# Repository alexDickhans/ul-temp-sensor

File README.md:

# Adaptive BLE Sensor Node System

A complete IoT sensor system featuring adaptive power management, BLE communication, and data logging. The system consists of a Raytac MDBT50Q (nRF52840) sensor node and a Raspberry Pi host application.

## 🏗️ System Architecture

```
┌─────────────────┐    BLE Advertisement    ┌─────────────────┐
│   Sensor Node   │ ──────────────────────► │  Raspberry Pi   │
│                 │                         │     Host        │
│ • nRF52840      │                         │                 │
│ • BME280        │                         │ • BLE Scanner   │
│ • Battery       │                         │ • Data Logger   │
│ • Adaptive PM   │                         │ • SQLite DB     │
└─────────────────┘                         └─────────────────┘
```

## 📋 Features

### MCU Firmware (nRF52840)
- **Adaptive Power Management**: 4-tier power system based on battery voltage
- **BME280 Integration**: Temperature, pressure, and humidity sensing
- **BLE Advertising**: Non-connectable advertisements with sensor data
- **Deep Sleep**: System OFF mode with RTC wake-up
- **Battery Monitoring**: ADC-based voltage sensing

### Raspberry Pi Host
- **BLE Scanner**: Continuous scanning for sensor advertisements
- **Data Decoding**: Parses manufacturer-specific data payloads
- **SQLite Database**: Local data storage with indexing
- **Data Viewer**: Query and display sensor data
- **Systemd Service**: Automatic startup and management

## 🔋 Power Management Tiers

| Tier | Battery Range | Wake Interval | BLE Rate | Description |
|------|---------------|---------------|----------|-------------|
| Normal | 4.2V - 3.8V | 5 minutes | 1 Hz | Full performance |
| Conserve | 3.8V - 3.6V | 15 minutes | 0.2 Hz | Reduced frequency |
| Reserve | 3.6V - 3.4V | 30 minutes | 0.1 Hz | Minimal operation |
| Survival | 3.4V - 3.2V | 60 minutes | 0.1 Hz | Critical battery |

## 📦 Hardware Requirements

### Sensor Node
- **MCU**: Raytac MDBT50Q (nRF52840 inside)
- **Sensor**: Bosch BME280 (I²C)
- **Battery**: Li-Po pouch (3.7V, 1000mAh+)
- **PMIC**: BQ25570 (solar charging)
- **Connections**: I²C, ADC, RTC

### Host System
- **Platform**: Raspberry Pi (any modern Pi with BLE)
- **OS**: Raspberry Pi OS or Ubuntu
- **Storage**: SD card with 8GB+ free space

## 🚀 Quick Start

### 1. MCU Firmware Setup

```bash
# Install nRF Connect SDK
# Follow: https://developer.nordicsemi.com/nRF_Connect_SDK/doc/latest/nrf/gs_installing.html

# Clone and build
cd mcu_firmware
./build.sh

# Flash to device
west flash -d build
```

### 2. Raspberry Pi Host Setup

```bash
# Install dependencies
sudo apt update
sudo apt install python3-pip python3-venv bluetooth bluez

# Create virtual environment
cd pi_host
python3 -m venv venv
source venv/bin/activate

# Install Python packages
pip install -r requirements.txt

# Run scanner
python3 sensor_scanner.py
```

### 3. View Data

```bash
# List known devices
python3 data_viewer.py --list-devices

# View recent data
python3 data_viewer.py --hours 24 --stats

# Filter by device
python3 data_viewer.py --device AA:BB:CC:DD:EE:FF
```

## 📊 BLE Data Format

The sensor node broadcasts manufacturer-specific data with the following structure:

```c
struct sensor_adv_data {
    uint8_t version;           // Protocol version (1)
    uint8_t tier;              // Power tier (0-3)
    uint16_t battery_mv;       // Battery voltage in mV
    int16_t temperature;       // Temperature * 100 (°C)
    uint16_t pressure;         // Pressure * 10 (hPa)
    uint16_t humidity;         // Humidity * 100 (%)
    uint32_t timestamp;        // Unix timestamp
};
```

**Company ID**: Nordic Semiconductor (0x0059)

## 🔧 Configuration

### MCU Configuration

Edit `mcu_firmware/prj.conf` for:
- BLE power settings
- I²C configuration
- ADC settings
- Power management options

### Host Configuration

Command-line options for `sensor_scanner.py`:
- `--db`: Database file path
- `--scan-duration`: BLE scan duration (seconds)
- `--log-level`: Logging verbosity

## 📈 Data Analysis

### Database Schema

```sql
CREATE TABLE sensor_data (
    id INTEGER PRIMARY KEY AUTOINCREMENT,
    device_address TEXT NOT NULL,
    device_name TEXT,
    timestamp DATETIME NOT NULL,
    temperature REAL,
    pressure REAL,
    humidity REAL,
    battery_mv INTEGER,
    power_tier INTEGER,
    rssi INTEGER,
    created_at DATETIME DEFAULT CURRENT_TIMESTAMP
);
```

### Example Queries

```sql
-- Average temperature by hour
SELECT strftime('%Y-%m-%d %H:00:00', timestamp) as hour,
       AVG(temperature) as avg_temp
FROM sensor_data 
GROUP BY hour 
ORDER BY hour DESC;

-- Battery status over time
SELECT timestamp, battery_mv, power_tier
FROM sensor_data 
WHERE device_address = 'AA:BB:CC:DD:EE:FF'
ORDER BY timestamp DESC;
```

## 🔍 Troubleshooting

### Common Issues

1. **No BLE advertisements detected**
   - Check device is powered and firmware is flashed
   - Verify BLE is enabled on Raspberry Pi
   - Check for interference or range issues

2. **High power consumption**
   - Verify deep sleep is working (measure current <3µA)
   - Check BLE advertising intervals
   - Monitor battery voltage thresholds

3. **Sensor reading errors**
   - Check I²C connections
   - Verify BME280 address (0x76 or 0x77)
   - Check power supply stability

### Debug Commands

```bash
# Monitor MCU serial output
west espressif monitor -d build

# Check BLE devices
sudo hcitool lescan

# Monitor system logs
journalctl -u sensor-scanner -f

# Check database integrity
sqlite3 sensor_data.db "PRAGMA integrity_check;"
```

## 🔄 Systemd Service

Create `/etc/systemd/system/sensor-scanner.service`:

```ini
[Unit]
Description=BLE Sensor Scanner
After=bluetooth.service
Wants=bluetooth.service

[Service]
Type=simple
User=pi
WorkingDirectory=/home/pi/sensor-system/pi_host
Environment=PATH=/home/pi/sensor-system/pi_host/venv/bin
ExecStart=/home/pi/sensor-system/pi_host/venv/bin/python sensor_scanner.py
Restart=always
RestartSec=10

[Install]
WantedBy=multi-user.target
```

Enable and start:
```bash
sudo systemctl enable sensor-scanner
sudo systemctl start sensor-scanner
```

## 📚 Development

### Project Structure

```
temp-sensor-code/
├── mcu_firmware/           # nRF52840 firmware
│   ├── src/               # Source files
│   ├── boards/            # Device tree overlays
│   ├── prj.conf          # Zephyr configuration
│   └── build.sh          # Build script
├── pi_host/              # Raspberry Pi application
│   ├── sensor_scanner.py # Main scanner
│   ├── data_viewer.py    # Data query tool
│   └── requirements.txt  # Python dependencies
└── README.md             # This file
```

### Adding New Sensors

1. Extend the `sensor_adv_data` structure
2. Update the Python decoder
3. Modify database schema
4. Update data viewer

### Power Optimization

- Use forced mode for BME280 (not continuous)
- Minimize BLE advertising duration
- Optimize RTC wake intervals
- Monitor current consumption with multimeter

## 📄 License

This project is open source. See LICENSE file for details.

## 🤝 Contributing

1. Fork the repository
2. Create a feature branch
3. Make your changes
4. Test thoroughly
5. Submit a pull request

## 📞 Support

For issues and questions:
- Check the troubleshooting section
- Review the code comments
- Open an issue on GitHub

---

**Note**: This system is designed for educational and prototyping purposes. For production use, consider additional security measures and environmental protection.

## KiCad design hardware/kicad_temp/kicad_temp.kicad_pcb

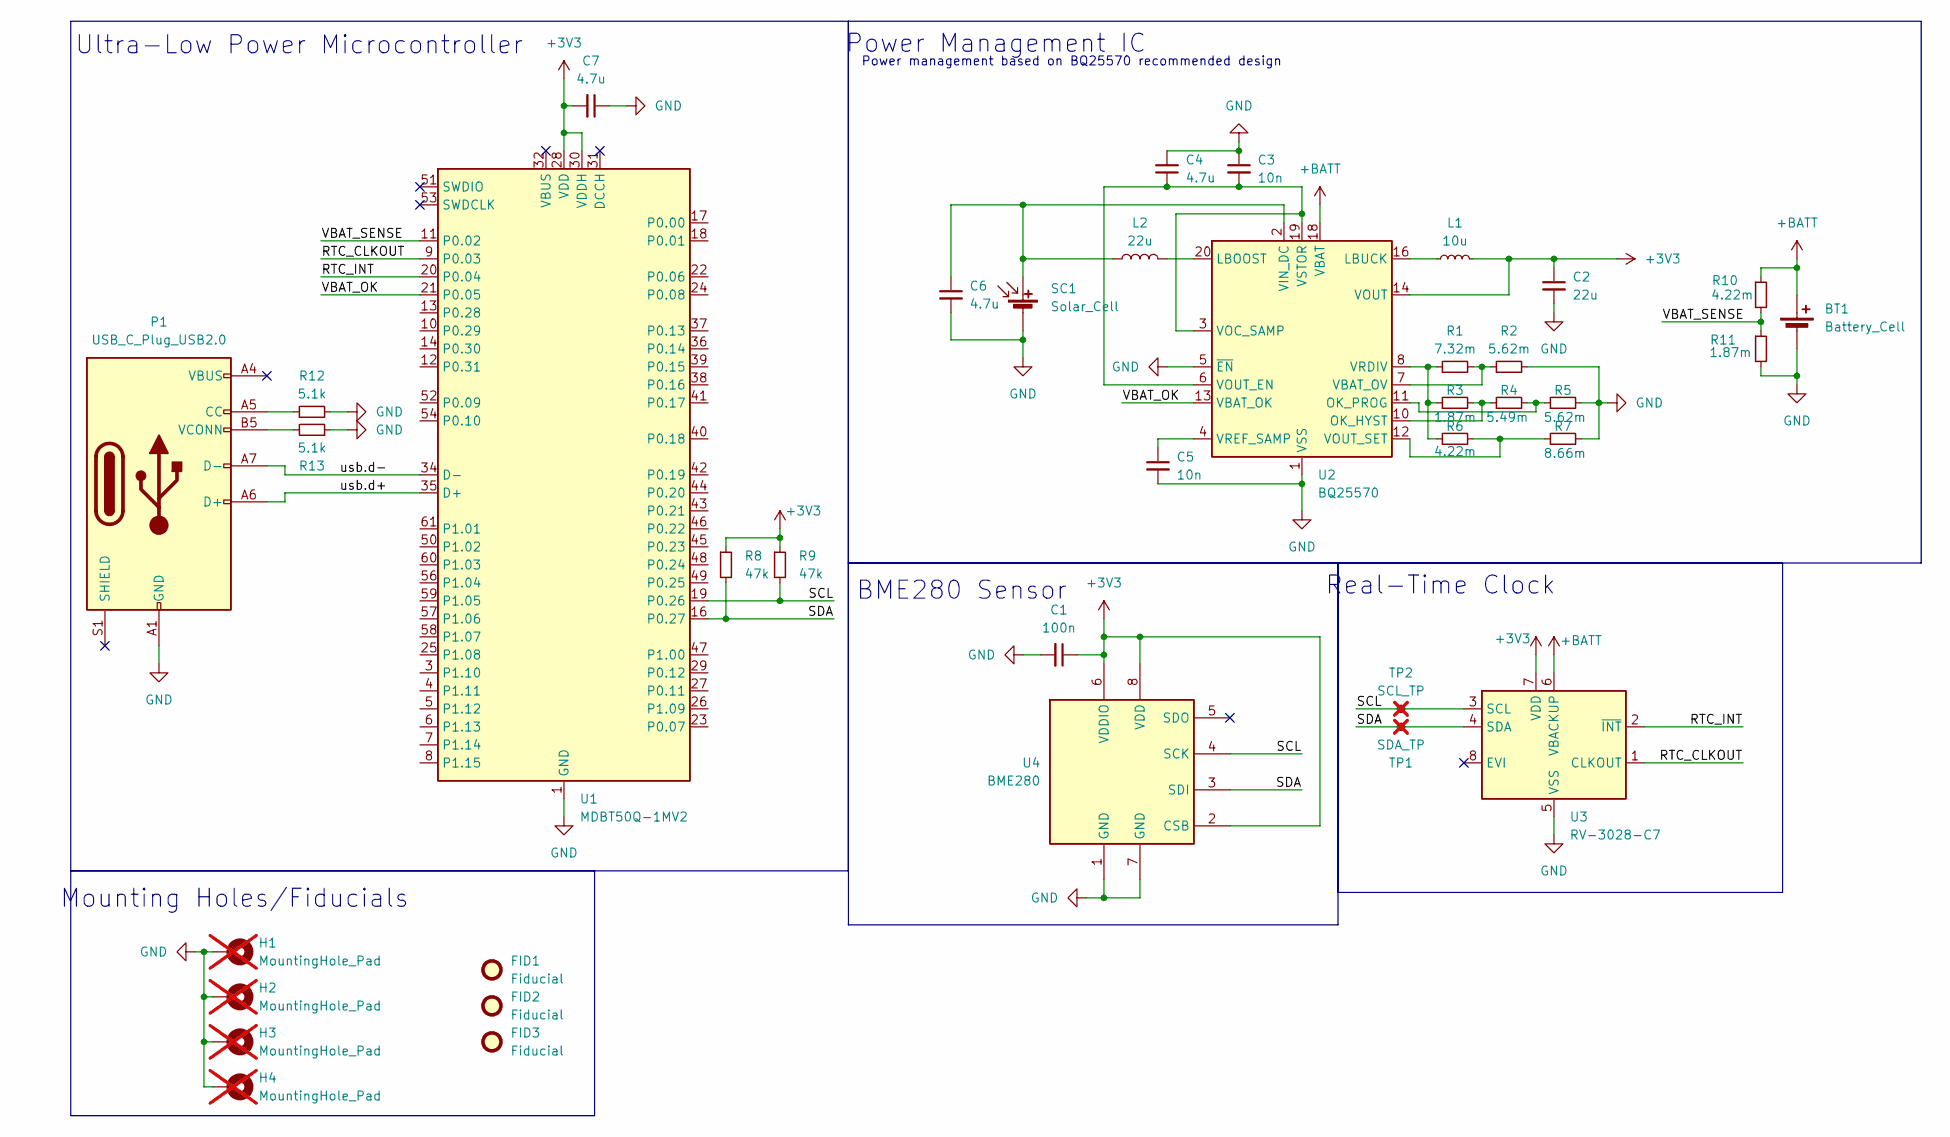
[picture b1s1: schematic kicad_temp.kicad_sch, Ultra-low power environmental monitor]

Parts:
BT1: Battery_Cell; PinHeader_1x02_P2.54mm_Vertical
C1: 100n; C_0603_1608Metric
C2: 22u; C_0603_1608Metric
C3, C5: 10n; C_0603_1608Metric
C4, C6, C7: 4.7u; C_0603_1608Metric
FID1, FID2, FID3: Fiducial; Fiducial_1.5mm_Mask3mm
H1, H2, H3, H4: MountingHole_Pad; MountingHole_3.2mm_M3_Pad; not fitted
L1: 10u; L_0805_2012Metric
L2: 22u; L_0805_2012Metric
P1: USB_C_Plug_USB2.0; USB_C_Receptacle_Molex_105450-0101
R1: 7.32m; R_0603_1608Metric
R2, R5: 5.62m; R_0603_1608Metric
R3, R11: 1.87m; R_0603_1608Metric
R4: 5.49m; R_0603_1608Metric
R6, R10: 4.22m; R_0603_1608Metric
R7: 8.66m; R_0603_1608Metric
R8, R9: 47k; R_0402_1005Metric
R12, R13: 5.1k; R_0402_1005Metric
SC1: Solar_Cell; PinHeader_1x02_P2.54mm_Vertical
TP1: SDA_TP; TestPoint_Pad_D2.0mm; not fitted
TP2: SCL_TP; TestPoint_Pad_D2.0mm; not fitted
U1: MDBT50Q-1MV2; Raytac_MDBT50Q
U2: BQ25570; QFN-20-1EP_3.5x3.5mm_P0.5mm_EP2x2mm
U3: RV-3028-C7; MicroCrystal_C7_SON-8_1.5x3.2mm_P0.9mm
U4: BME280; Bosch_LGA-8_2.5x2.5mm_P0.65mm_ClockwisePinNumbering

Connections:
+3V3: C1.1, C2.1, C7.2, L1.2, R8.1, R9.1, U1.28 (VDD), U1.30 (VDDH), U2.14 (VOUT), U3.7 (VDD), U4.2 (CSB), U4.6 (VDDIO), U4.8 (VDD)
+BATT: BT1.1 (+), R10.1, U2.18 (VBAT), U3.6 (VBACKUP)
/RTC_CLKOUT: U1.9 (P0.03), U3.1 (CLKOUT)
/RTC_INT: U1.20 (P0.04), U3.2 (~INT)
/SCL: R9.2, TP2.1, U1.19 (P0.26), U3.3 (SCL), U4.4 (SCK)
/SDA: R8.2, TP1.1, U1.16 (P0.27), U3.4 (SDA), U4.3 (SDI)
/VBAT_OK: U1.21 (P0.05), U2.13 (VBAT_OK)
/VBAT_SENSE: R10.2, R11.1, U1.11 (P0.02)
/usb.d+: P1.A6 (D+), U1.35 (D+)
/usb.d-: P1.A7 (D-), U1.34 (D-)
GND: BT1.2 (-), C1.2, C2.2, C3.1, C4.2, C5.2, C6.2, C7.1, H1.1, H2.1, H3.1, H4.1, P1.A1 (GND), P1.A12 (GND), P1.B1 (GND), P1.B12 (GND), R2.2, R5.2, R7.2, R11.2, R12.2, R13.1, SC1.2 (-), U1.1 (GND), U1.2 (GND), U1.15 (GND), U1.33 (GND), U1.55 (GND), U2.1 (VSS), U2.5 (~EN), U2.9 (VSS), U2.15 (VSS), U2.17 (VSS), U2.21 (VSS), U3.5 (VSS), U4.1 (GND), U4.7 (GND)
unnamed: P1.A5 (CC), R12.1
unnamed: P1.B5 (VCONN), R13.2
unnamed: C6.1, L2.1, SC1.1 (+), U2.2 (VIN_DC)
unnamed: L2.2, U2.20 (LBOOST)
unnamed: L1.1, U2.16 (LBUCK)
unnamed: R3.2, R4.1, U2.10 (OK_HYST)
unnamed: R4.2, R5.1, U2.11 (OK_PROG)
unnamed: R1.2, R2.1, U2.7 (VBAT_OV)
unnamed: C3.2, C4.1, U2.3 (VOC_SAMP), U2.6 (VOUT_EN), U2.19 (VSTOR)
unnamed: R6.2, R7.1, U2.12 (VOUT_SET)
unnamed: R1.1, R3.1, R6.1, U2.8 (VRDIV)
unnamed: C5.1, U2.4 (VREF_SAMP)

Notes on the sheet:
Power management based on BQ25570 recommended design
Power Management IC
Ultra-Low Power Microcontroller
Mounting Holes/Fiducials
Real-Time Clock
BME280 Sensor

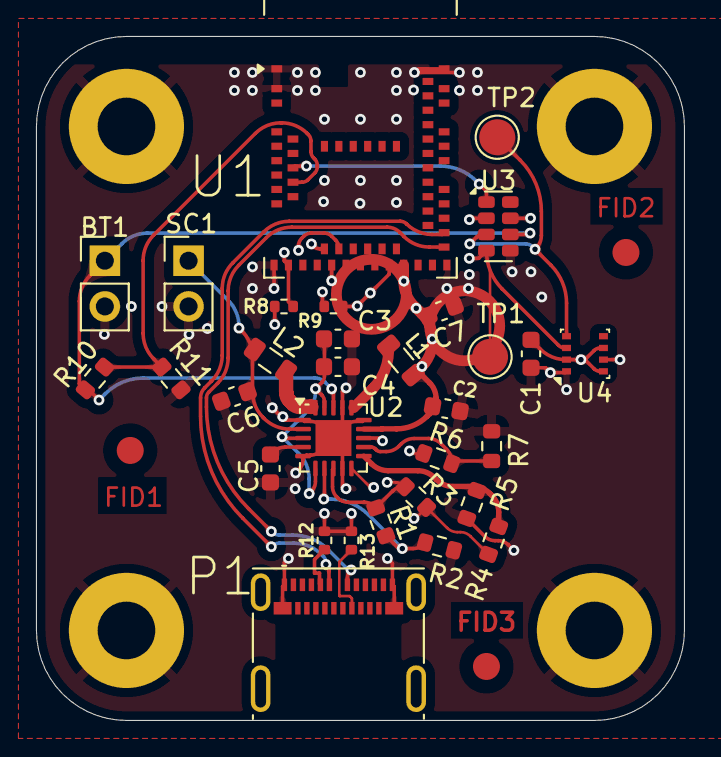
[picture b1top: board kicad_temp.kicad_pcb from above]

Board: 4 copper layers, 36.0 x 38.0 mm, 38 parts (0 on the bottom side), 23 nets.

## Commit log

2025-08-29 Add .gitignore
2025-08-29 Add docker and kicad files
